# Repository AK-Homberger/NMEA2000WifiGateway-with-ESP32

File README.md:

# NMEA2000 Wifi Gateway with ESP32
This repository shows how to build a NMEA2000 WiFi Gateway with AIS multiplexing and voltage/temperature alarms.
The ESP32 in this project is an ESP32 NODE MCU from AzDelivery. Pin layout for other ESP32 devices might differ.

The Gateway supports the following functions:

- Providing a WiFi Access Point for other systems like tablets or computer (e.g. with OpenCPN).
- Alternatively it can also connect as client to a WLAN network (set WLAN_CLIENT to 1 to enable).
- Forwarding navigation information from NMEA2000 to NMEA0183 as TCP stream (including log, water temp, and rudder information).
- Calculating TWS/TWD from apparent wind information and heading/COG). This allows use of OpenCPN WindHistory Dashbord instument.
- Forwarding serial NMEA0183 AIS information (on RX2) as UDP broadcast stream (for Navionics on tablets, but also for OpenCPN).
- Mutiplexing AIS information into TCP streams (to support applications that can handle only one (TCP) connection.
- Sending battery voltage and fridge temperature as NMEA2000 sentence (engine dynamic parameter PGN, my eS75 Ramarine MFD shows this as cooling temperature and alternator voltage).
- Battery voltage is measured with the ESP32 ADC.
- Fridge temperature with a Dallas DS18B20 OneWire sensor (easily extendable with more sensors).
- True parallel processing: Reading OneWire sensor as isolated task on second core of ESP32 (sensor reading is blocking for about 750 ms).
- Checking voltage and temperature levels against predefined values and generating an alarm with a piezo alarm buzzer.
- Acknowledgement of alarm with a button.
- Showing fridge temperature in web browser (nice JavaScript gauge).
- JSON interface on port 90 to request NMEA2000 data via JSON request (see M5Stack Display repository for example on usage).

The code is based on the NMEA 2000 / NMEA0183 libraries from Timo Lappalainen (https://github.com/ttlappalainen).
Download and install the libraries from GitHub link above:

- NMEA2000
- NMEA2000_esp32
- NMEA0183

The Gateway is using the following additional libraries (to be installed with the Arduiono IDE Library Manager):

- OneWire
- OneButton
- DallasTemperature
- ArduinoJson (Please use current version 6.x.x from now on)

For the ESP32 CAN bus, I used the "Waveshare SN65HVD230 Can Board" as transceiver. It works well with the ESP32.
For the Gateway, I use the pins GPIO4 for CAN RX and GPIO5 for CAN TX. The standard configuration of the NMEA2000 library would block the Serial2 connection used for AIS.

# !!!Caution!!! 
The former versions used Pin2 for TX. But I noticed problems with the NMEA2000 bus during reboot/programming of the ESP32. It looks like pin 2 is used during reboot and also during programming. A reboot confused the wind instrument (no TWS). With this new configuration evrything works without problems.

The 12 Volt is reduced to 5 Volt with a DC Step-Down_Converter (D24V10F5, https://www.pololu.com/product/2831).

The ADC of the ESP32 is a bit difficult to handle. You have to set the calibration information in the code according to the real values of the resistors at the ADC input of the ESP 32 (e.g. 15 for 100K / 27K which gives a range from 0 to 15 Volt).

# Configuration
To adjust the program to your need please change the following values in the code:

```
#define ENABLE_DEBUG_LOG 0 // Debug log, set to 1 to enable AIS forward on USB-Serial / 2 for ADC voltage to support calibration
#define UDP_Forwarding 0   // Set to 1 for forwarding AIS from serial2 to UDP brodcast
#define HighTempAlarm 12   // Alarm level for fridge temperature (higher)
#define LowVoltageAlarm 11 // Alarm level for battery voltage (lower)

#define ADC_Calibration_Value 34.3 // The real value depends on the true resistor values for the ADC input (100K / 27 K)

#define WLAN_CLIENT 0  // Set to 1 to enable client network. 0 to act as AP only

// Wifi cofiguration Client and Access Point
const char *AP_ssid = "MyESP32";  // ESP32 as AP
const char *CL_ssid = "MyWLAN";   // ESP32 as client in network

const char *AP_password = "appassword";   // AP password. Must be longer than 7 characters
const char *CL_password = "clientpassword";  // Client password

// Put IP address details here
IPAddress AP_local_ip(192, 168, 15, 1);  // Static address for AP
IPAddress AP_gateway(192, 168, 15, 1);
IPAddress AP_subnet(255, 255, 255, 0);

IPAddress CL_local_ip(192, 168, 1, 10);  // Static address for Client Network. Please adjust to your AP IP and DHCP range!
IPAddress CL_gateway(192, 168, 1, 1);
IPAddress CL_subnet(255, 255, 255, 0);
```

Schematics and PCB details are in the KiCAD folder (to allow modifications). The board can also be ordered at Aisler.net: https://aisler.net/p/DNXXRLFU

# Be careful with placing the the ESP32 on the PCB. The USB connector has to be on the right side.

Fridge temperature is also shown with a nice web gauge:

# Remove the 120 ohm resistor from the transceiver
For unknown reasons, many CAN bus transceivers for the ESP32 have a 120 Ohm resistor built into them. The resistor does not belong to the devices at the ends of the stub lines, but to the ends of the backbone cable.

Whether the transceiver contains a 120 ohm resistor can be determined either by looking at the [circuit diagram](https://github.com/AK-Homberger/NMEA2000-Workshop/blob/main/Docs/SN65HVD230%20CAN%20Board_SCH.pdf) or by measuring with the multimeter.

A knife tip is suitable for removing the SMD resistor. Use it to scratch or pry off the resistance. With the transceiver shown here, place the tip of the knife in front of the resistor (between the chip and the resistor) and support the knife against the chip. Then lever the tip against the resistance and use it to scratch / loosen / break the resistance. Whichever happens first.

It then looks like the picture. Then measure to be on the safe side. Without a 120 ohm resistor, the multimeter shows approx. 75 kOhm.

# Parts:

- Board [Link](https://aisler.net/p/DNXXRLFU)
- U1 ESP32 [Link](https://www.amazon.de/AZDelivery-NodeMCU-Development-Nachfolgermodell-ESP8266/dp/B071P98VTG/ref=sxts_sxwds-bia-wc-drs3_0?__mk_de_DE=%C3%85M%C3%85%C5%BD%C3%95%C3%91&cv_ct_cx=ESP32&dchild=1&keywords=ESP32) 
- J5 SN65HVD230 [Link](https://eckstein-shop.de/WaveshareSN65HVD230CANTransceiverBoard33V2CESDProtection)
- J2 D24V10F5 [Link](https://eckstein-shop.de/Pololu5V2C1AStep-DownSpannungsreglerD24V10F5)
- B1 Buzzer [Link](https://www.reichelt.de/de/en/developer-boards-active-piezo-buzzer-module-debo-piezo-p239111.html?&nbc=1)
- R1 Resistor 3,3 KOhm [Link](https://www.reichelt.de/de/en/carbon-film-resistor-1-4-w-5-3-3-ohm-1-4w-3-3-p1396.html?&nbc=1)
- R2 Resistor 100 KOhm [Link](https://www.reichelt.de/de/en/carbon-film-resistor-1-4w-5-100-kilo-ohms-1-4w-100k-p1337.html?&nbc=1)
- R3 Resistor 27 KOhm [Link](https://www.reichelt.de/de/en/carbon-film-resistor-1-4-w-5-27-kohm-1-4w-27k-p1392.html?&nbc=1)
- R4, R6 Resistor 4,7 KOhm [Link](https://www.reichelt.de/de/en/carbon-film-resistor-1-4-w-5-4-7-kohm-1-4w-4-7k-p1425.html?&nbc=1)
- R5 Resistor 33 KOhm [Link](https://www.reichelt.de/de/en/carbon-film-resistor-1-4-w-5-33-kohm-1-4w-33k-p1412.html?&nbc=1)
- Q1, Q2 Transistor BC547 [Link](https://www.reichelt.de/de/en/small-signal-transistors-npn-to-92-45-v-rnd-bc547-p223356.html?&nbc=1)
- D1 Diode 1N4001 [Link](https://www.reichelt.com/de/en/rectifier-diode-do41-50-v-1-a-1n-4001-p1723.html?&nbc=1)
- D2 Diode 1N4148 [Link](https://www.reichelt.de/schalt-diode-100-v-150-ma-do-35-1n-4148-p1730.html?search=1n4148)
- SW1 Push button [Link](https://www.reichelt.de/miniatur-drucktaster-0-5a-24vac-1x-ein-rt-t-250a-rt-p31772.html?&trstct=pol_12&nbc=1)
- DS18B20 [Link](https://www.reichelt.com/shelly-temperatur-sensor-ds18b20-shelly-ds18b20-p287127.html?&trstct=pos_1&nbc=1)
- J4 Connector 3-pin [Link](https://www.reichelt.de/de/en/3-pin-terminal-strip-spacing-5-08-akl-101-03-p36606.html?&nbc=1)
- J1, J3 Connector 2-pin [Link](https://www.reichelt.de/de/en/2-pin-terminal-strip-spacing-5-08-akl-101-02-p36605.html?&nbc=1)
- Housing [Link](https://www.reichelt.de/de/en/plastic-housing-series-1591-57-x-87-x-36-mm-black-1591xxlsbk-p221267.html?&nbc=1)

# Updates:
- 06.11.20: Version 1.3: Changed PCB layout to version 1.1. Larger terminal blocks and different transistor footprints for easy soldering.
- 01.11.20: Version 1.3: Added KiCAD files.
- 04.08.20: Version 1.3: Changed CAN_TX to 5. Added WLAN client mode. Store last Node Address.
- 24.07.20: Version 1.2: Fixed AP setting problem (sometimes 192.168.4.1 was set after reboot).
- 23.07.20: Version 1.1: Moved to new JSON library version 6.x.x.
- 23.07.20: Version 1.0: Changed task 0 priority to 0 (see Issues) and corrected TWA calculation.
- 11.12.19: Version 0.9: Added CAN pin definition in code. No need to change settings in include file of library.
- 17.10.19: Version 0.8. Increase JSON buffer improved ID calculation.
- 14.10.19: Version 0.7. Added JSON interface on port 90. Added unique ID.
- 16.09.19: Added GGA sentence in N2kDataToNMEA0183.cpp
- 03.08.19: Version 0.4. Added rudder, log information. Calculate TWS/TWD from apparent wind, heading and COG. Added web gauge for fridge temperature (web browser, port 80).
- 23.07.19: Version 0.2 fixes the full AIS message forwarding issue. I'm now using the GetMessage function from the MNEA0183 library.

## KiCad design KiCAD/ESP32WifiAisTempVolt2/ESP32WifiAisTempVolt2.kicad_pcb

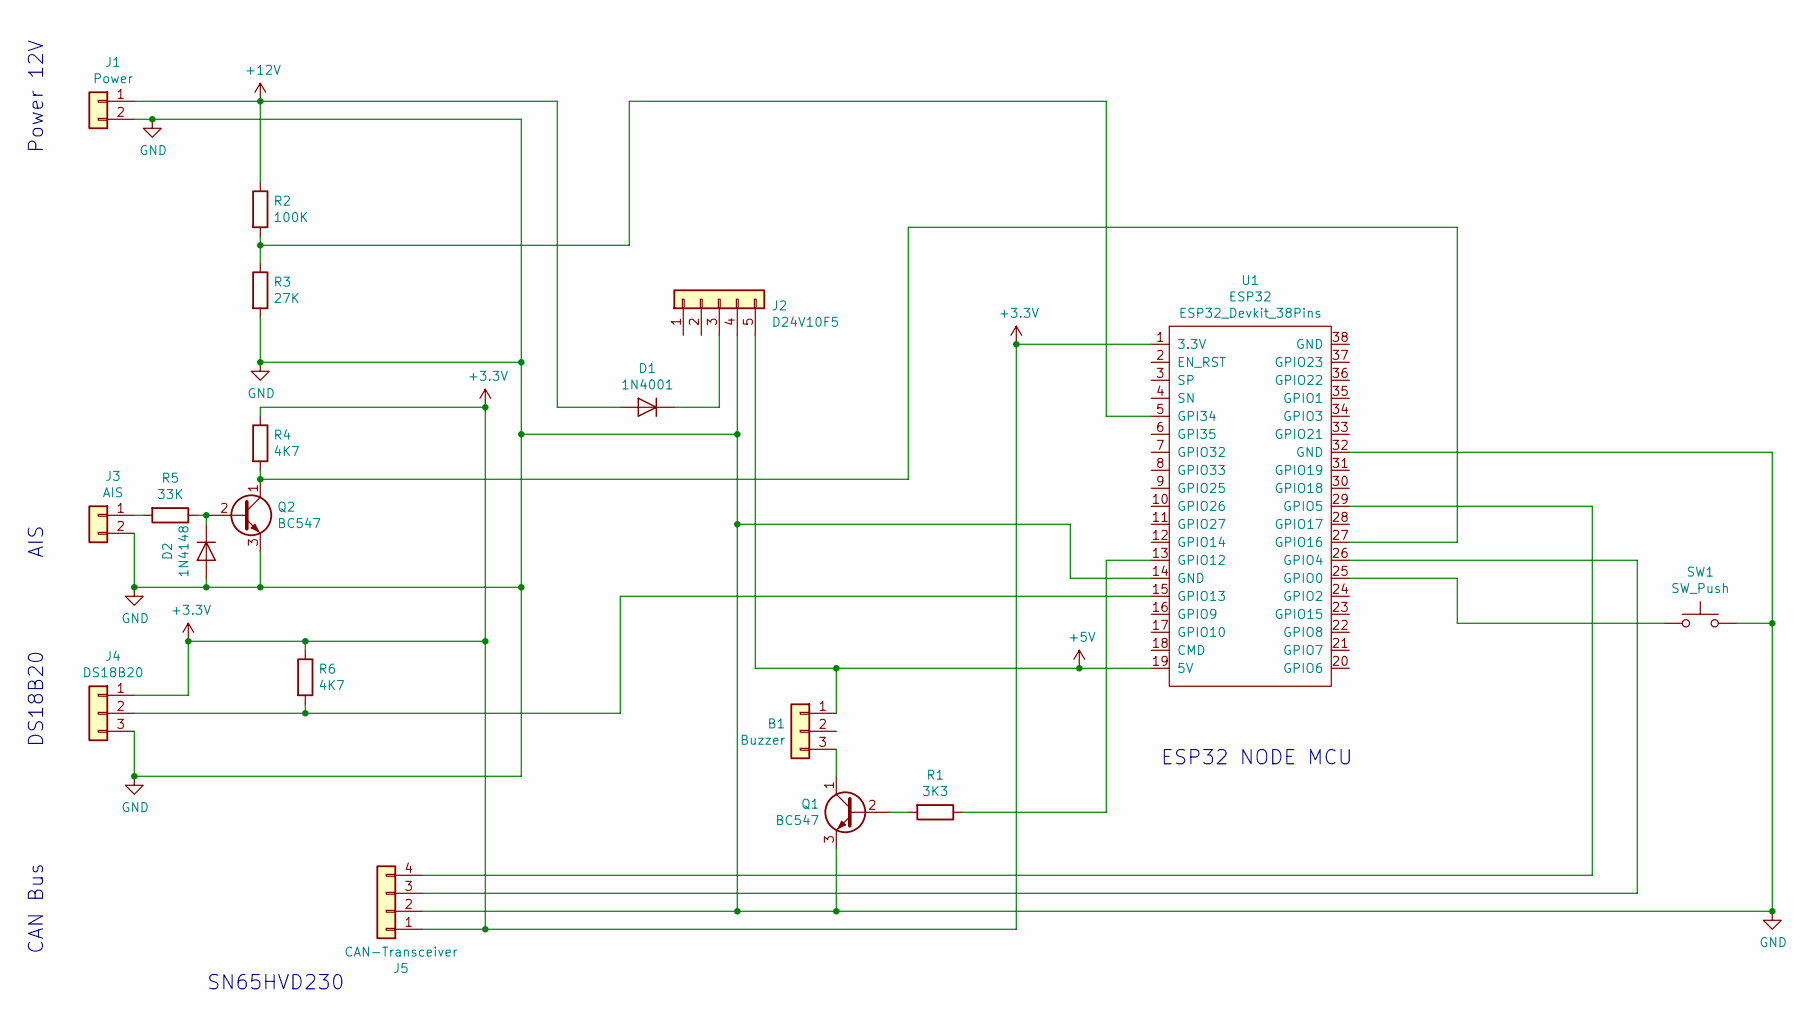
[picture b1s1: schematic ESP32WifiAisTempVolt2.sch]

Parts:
B1: Buzzer; PinHeader_1x03_P2.54mm_Vertical
D1: 1N4001; D_DO-41_SOD81_P10.16mm_Horizontal
D2: 1N4148; D_DO-41_SOD81_P7.62mm_Horizontal
J1: Power; TerminalBlock_bornier-2_P5.08mm
J2: D24V10F5; PinHeader_1x05_P2.54mm_Vertical
J3: AIS; TerminalBlock_bornier-2_P5.08mm
J4: DS18B20; TerminalBlock_bornier-3_P5.08mm
J5: CAN-Transceiver; PinHeader_1x04_P2.54mm_Vertical
Q1, Q2: BC547; TO-92_HandSolder
R1: 3K3; R_Axial_DIN0207_L6.3mm_D2.5mm_P7.62mm_Horizontal
R2: 100K; R_Axial_DIN0207_L6.3mm_D2.5mm_P7.62mm_Horizontal
R3: 27K; R_Axial_DIN0207_L6.3mm_D2.5mm_P7.62mm_Horizontal
R4, R6: 4K7; R_Axial_DIN0207_L6.3mm_D2.5mm_P7.62mm_Horizontal
R5: 33K; R_Axial_DIN0207_L6.3mm_D2.5mm_P7.62mm_Horizontal
SW1: SW_Push; PinHeader_1x02_P2.54mm_Vertical
U1: ESP32; ESP32_Devkit_38Pins

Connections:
+3V3: J4.1, J5.1, R4.1, R6.1, U1.1 (3.3V)
+5V: B1.1, J2.5, U1.19 (5V)
+12V: D1.2 (A), J1.1, R2.1
GND: D2.2 (A), J1.2, J2.4, J3.2, J4.3, J5.2, Q1.3 (E), Q2.3 (E), R3.2, SW1.2, U1.14 (GND), U1.32 (GND)
unnamed: B1.3, Q1.1 (C)
unnamed: D1.1 (K), J2.3
unnamed: D2.1 (K), Q2.2 (B), R5.1
unnamed: J3.1, R5.2
unnamed: J4.2, R6.2, U1.15 (GPIO13)
unnamed: J5.3, U1.26 (GPIO4)
unnamed: J5.4, U1.29 (GPIO5)
unnamed: Q1.2 (B), R1.2
unnamed: Q2.1 (C), R4.2, U1.27 (GPIO16)
unnamed: R1.1, U1.13 (GPIO12)
unnamed: R2.2, R3.1, U1.5 (GPI34)
unnamed: SW1.1, U1.25 (GPIO0)

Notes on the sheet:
ESP32 NODE MCU
SN65HVD230
CAN Bus
Power 12V
DS18B20
AIS

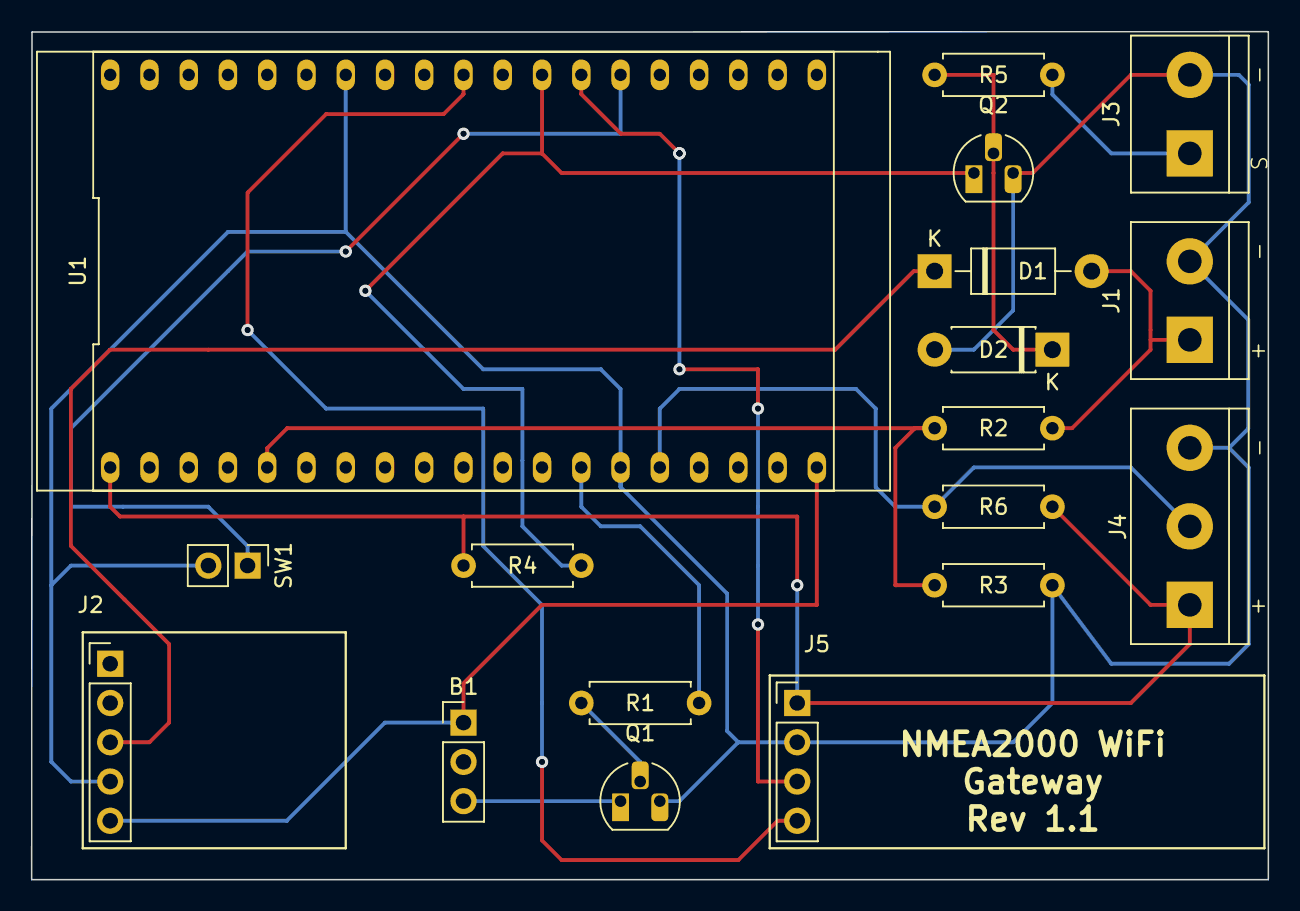
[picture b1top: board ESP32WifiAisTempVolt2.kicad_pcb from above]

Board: 2 copper layers, 80.0 x 54.9 mm, 18 parts (0 on the bottom side), 16 nets.

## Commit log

2019-07-23 Add files via upload
    Version 0.2, Fixing complete AIS message reead/write.
2019-08-03 Add files via upload
    Verion 0.4. Added Rudder and water Temp plus TWD/TWS. Web gauge for fridge temp.
2019-08-03 Update Wifi-Serial-AP-AIS-CAN.ino
    Added static IP for Navionics compatibility.
2019-08-11 Update Wifi-Serial-AP-AIS-CAN.ino
    Typos corrected.
2019-09-16 Add files via upload
    Added GGA sentence.
2019-09-16 Added GGA sentence in N2kDataToNMEA0183.cpp
2019-10-14 Added JSON Interface and ID
2019-10-14 Added JSON Interface on port 90
2019-10-14 Added JSON Interface and unique ID
2019-10-17 Increased JSON buffer, improved id calculation.
2019-10-17 Corrected errors with BoatData
2019-10-17 Corrected error with BoatData
2019-12-11 Added CAN pin definition.
2020-01-07 Added library information
2020-01-07 Added library information.
2020-01-09 KiCad schematics
2020-01-09 Added KiCad schematics
2020-02-01 Create LICENSE
2020-03-03 Corrected GND connection.
2020-07-23 Corrected True Wind Angle calculation.
2020-07-23 Changes priority for GetTemperature task (core 0) to 0 to avoid delays fo task 1 (loop() task).
2020-07-23 Moved to current JSON library version (6.x.x.)
2020-07-24 Fixed AP setting problem
2020-08-04 Changed ESP32_CAN_TX_PIN from 2 to 5!
2020-08-04 Changed CAN_TX to 5. Added WLAN client mode. Store last Node Address.
2020-11-01 Added KiCAD files
2020-11-06 Version 1.1
2022-02-05 Use new ESP32-API function name "esp_efuse_mac_get_default(chipid);"
